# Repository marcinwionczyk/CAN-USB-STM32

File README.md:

# CAN-USB-STM32
this is a repository based on "TheRo0T/CAN-USB-STM32" repository. The difference is that I'm using STM32F303CCT6 microcontroller, SN65HVD230DR CAN interface and my own PCB design based on available parts.

PCBs was designed with Autodesk Eagle.

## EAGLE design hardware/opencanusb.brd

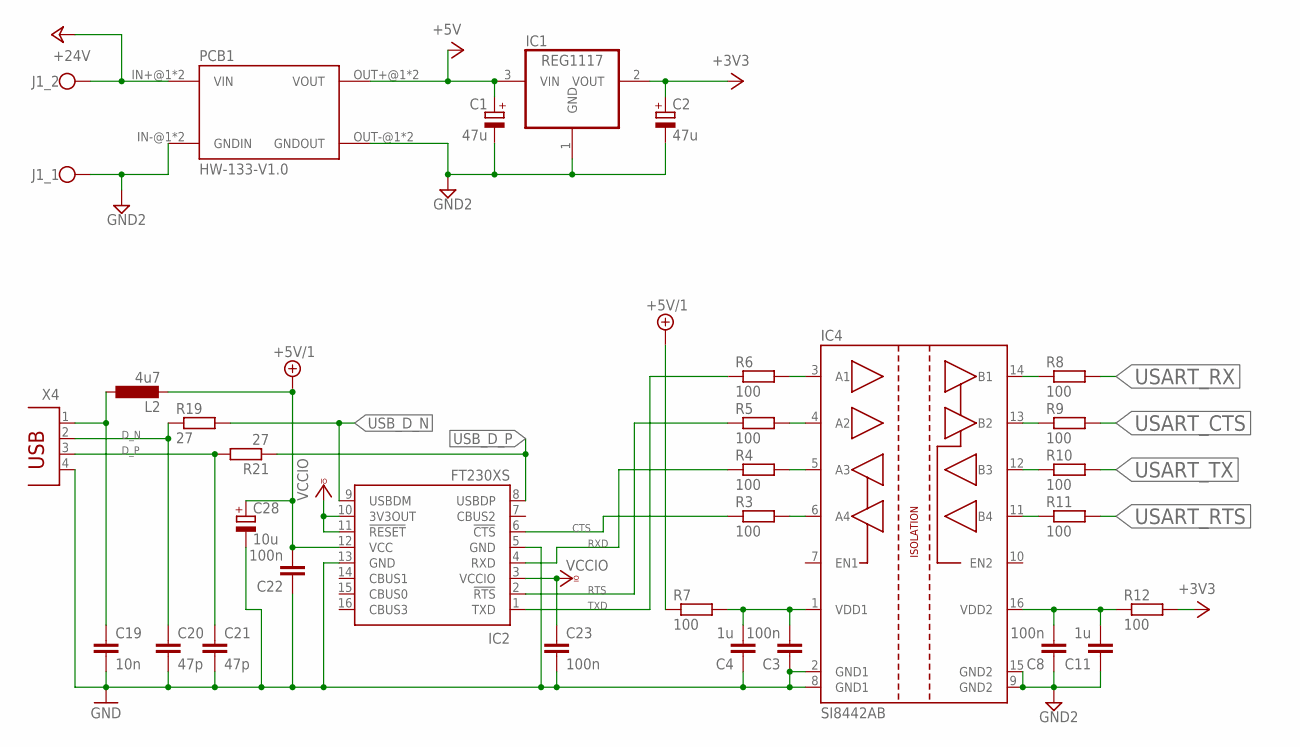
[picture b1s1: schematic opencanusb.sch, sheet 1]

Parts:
C1, C2: 47u; E1,8-4
C3, C8, C22, C23: 100n; C0805
C4, C11: 1u; C0805
C19: 10n; C0402
C20, C21: 47p; C0603
C28: 10u; SMC_A
IC1: REG1117; SOT223
IC2: FT230XS; SSOP16
IC4: SI8442AB; SOIC127P1030X265-16N
J1: DG300-7.5
L2: 4u7; L1812
PCB1: HW-133-V1.0; HW-133
R3, R4, R5, R6, R7, R8, R9, R10, R11, R12: 100; R0603
R19, R21: 27; R0805
X4: PN61729

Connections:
+3V3: C2.+, IC1.2 (VOUT), R12.2; also elsewhere on the board
+5V: C1.+, IC1.3 (VIN), PCB1.OUT+@1 (VOUT), PCB1.OUT+@2 (VOUT)
+5V/1: C22.2, C28.+, IC2.12 (VCC), L2.2, R7.1
+24V: J1.P$2, PCB1.IN+@1 (VIN), PCB1.IN+@2 (VIN)
CTS: IC2.6 (!CTS), R3.1
D_N: C20.1, R19.1, X4.2
D_P: C21.1, R21.2, X4.3
GND: C3.1, C4.1, C19.2, C20.2, C21.2, C22.1, C23.2, C28.-, IC2.5 (GND), IC2.13 (GND), IC4.2 (GND1), IC4.8 (GND1), X4.4
GND2: C1.-, C2.-, C8.1, C11.1, IC1.1 (GND), IC4.9 (GND2), IC4.15 (GND2), J1.P$1, PCB1.IN-@1 (GNDIN), PCB1.IN-@2 (GNDIN), PCB1.OUT-@1 (GNDOUT), PCB1.OUT-@2 (GNDOUT); also elsewhere on the board
unnamed: IC4.6 (A4), R3.2
unnamed: C3.2, C4.2, IC4.1 (VDD1), R7.2
unnamed: IC4.5 (A3), R4.2
unnamed: IC4.4 (A2), R5.2
unnamed: IC4.3 (A1), R6.2
unnamed: C8.2, C11.2, IC4.16 (VDD2), R12.1
unnamed: IC4.14 (B1), R8.1
unnamed: IC4.13 (B2), R9.1
unnamed: IC4.12 (B3), R10.1
unnamed: IC4.11 (B4), R11.1
unnamed: C19.1, L2.1, X4.1
RTS: IC2.2 (!RTS), R5.1
RXD: IC2.4 (RXD), R4.1
TXD: IC2.1 (TXD), R6.1
USART_CTS: R9.2; also elsewhere on the board
USART_RTS: R11.2; also elsewhere on the board
USART_RX: R8.2; also elsewhere on the board
USART_TX: R10.2; also elsewhere on the board
USB_D_N: IC2.9 (USBDM), R19.2
USB_D_P: IC2.8 (USBDP), R21.1
VCCIO: C23.1, IC2.3 (VCCIO), IC2.10 (3V3OUT), IC2.11 (!RESET)

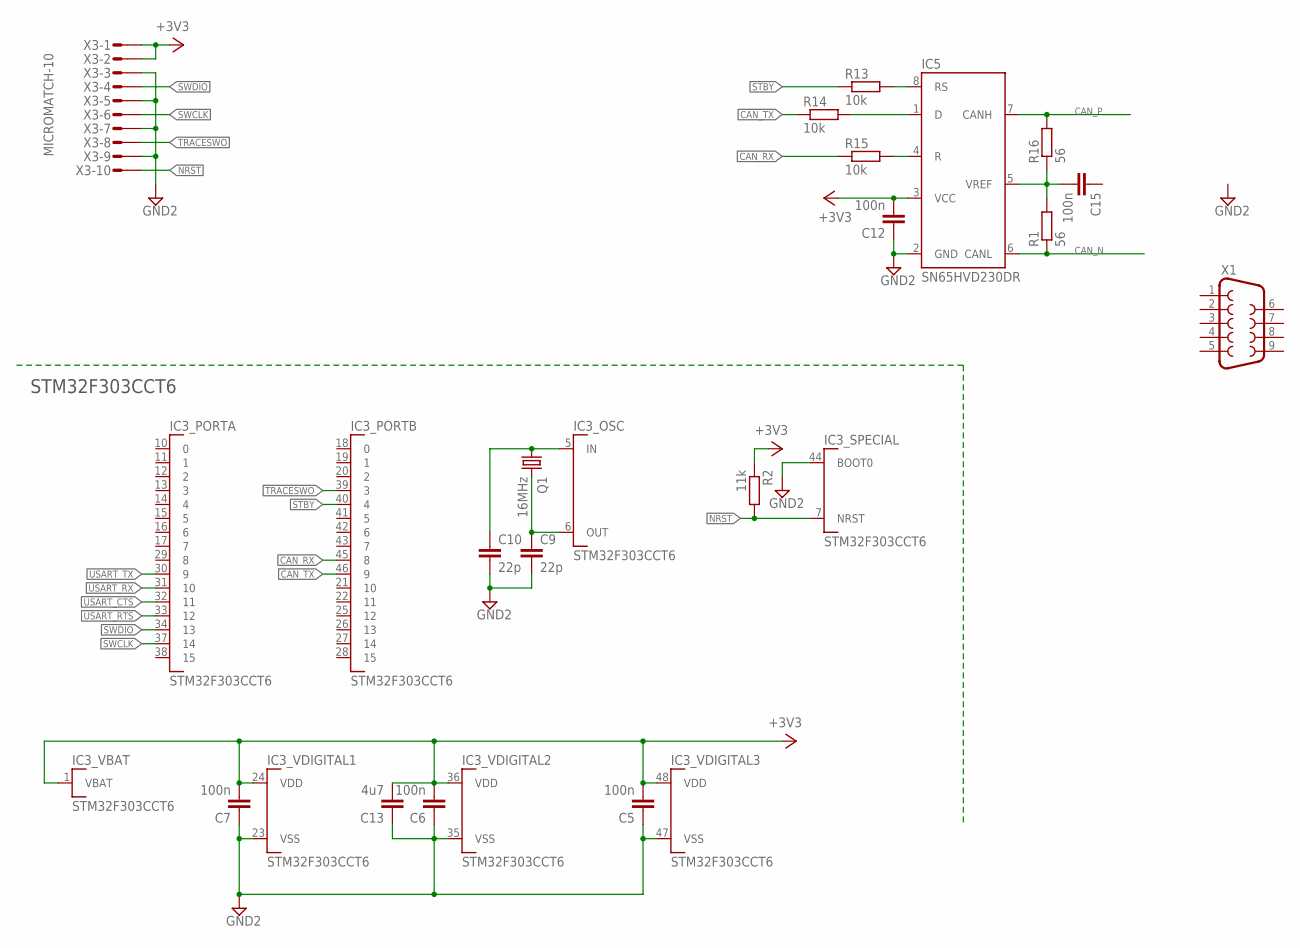
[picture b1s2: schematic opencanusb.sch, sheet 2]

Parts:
C5, C6, C7, C15: 100n; C0805
C9, C10: 22p; C0805
C12: 100n; C0402
C13: 4u7; C0805
IC3: STM32F303CCT6; QFP50P900X900X160-48N
IC5: SN65HVD230DR; SOIC127P599X175-8N
Q1: 16MHz; HC49UP
R1, R16: 56; R1206
R2: 11k; R1206
R13, R14, R15: 10k; R1206
X1: F09HP
X3: MICROMATCH-10

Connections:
+3V3: C5.2, C6.2, C7.2, C12.2, C13.2, IC3.1 (VBAT), IC3.24 (VDD), IC3.36 (VDD), IC3.48 (VDD), IC5.3 (VCC), R2.1, X3.1, X3.2; also elsewhere on the board
CAN_N: IC5.6 (CANL), R1.1
CAN_P: IC5.7 (CANH), R16.2
CAN_RX: IC3.45 (8), R15.1
CAN_TX: IC3.46 (9), R14.1
GND2: C5.1, C6.1, C7.1, C9.2, C10.2, C12.1, C13.1, IC3.23 (VSS), IC3.35 (VSS), IC3.44 (BOOT0), IC3.47 (VSS), IC5.2 (GND), X3.3, X3.5, X3.7, X3.9; also elsewhere on the board
unnamed: C15.2, IC5.5 (VREF), R1.2, R16.1
unnamed: IC5.8 (RS), R13.2
unnamed: IC5.1 (D), R14.2
unnamed: IC5.4 (R), R15.2
unnamed: C9.1, IC3.6 (OUT), Q1.2
unnamed: C10.1, IC3.5 (IN), Q1.1
NRST: IC3.7 (NRST), R2.2, X3.10
STBY: IC3.40 (4), R13.1
SWCLK: IC3.37 (14), X3.6
SWDIO: IC3.34 (13), X3.4
TRACESWO: IC3.39 (3), X3.8
USART_CTS: IC3.32 (11); also elsewhere on the board
USART_RTS: IC3.33 (12); also elsewhere on the board
USART_RX: IC3.31 (10); also elsewhere on the board
USART_TX: IC3.30 (9); also elsewhere on the board
VDDA: IC3.9 (VDDA)
VSSA: IC3.8 (VSSA)

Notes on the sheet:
STM32F303CCT6

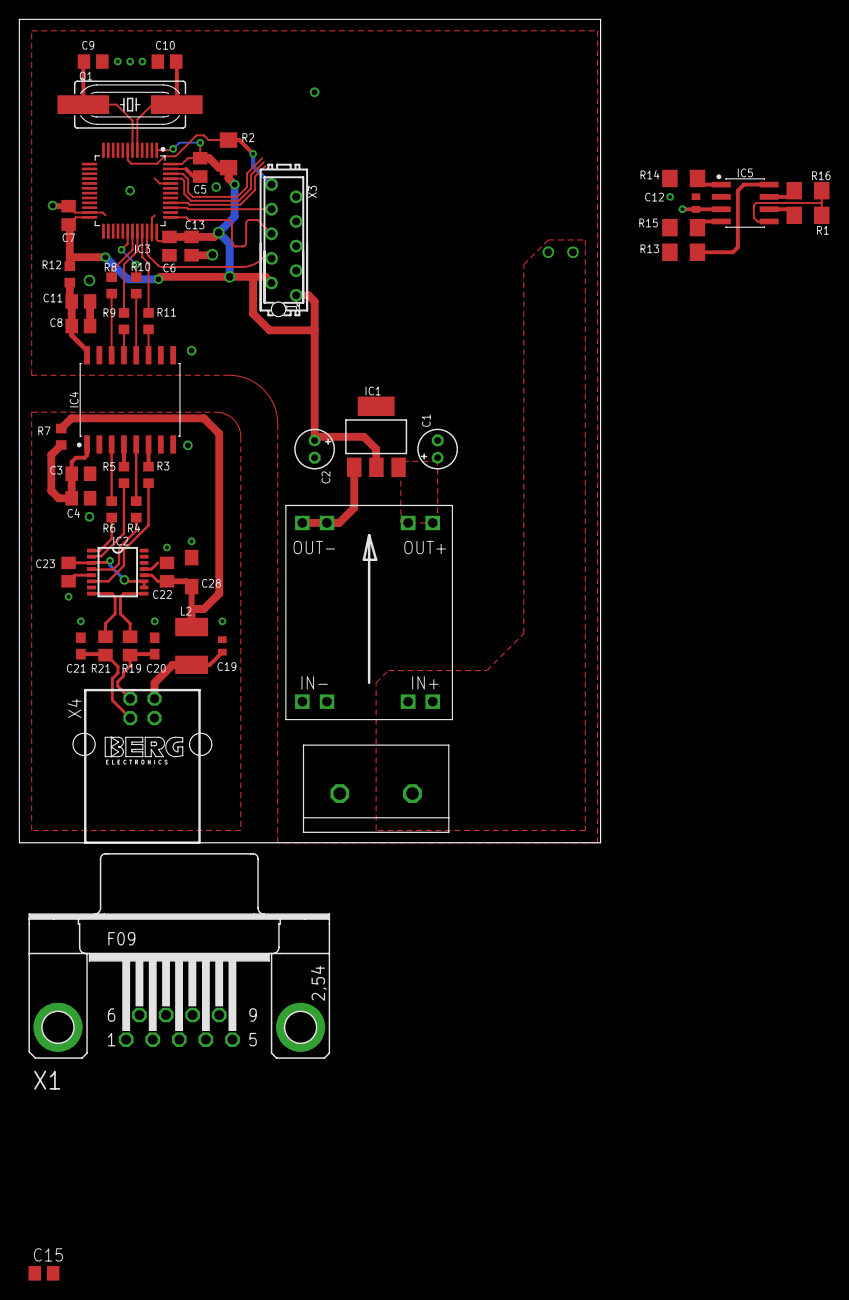
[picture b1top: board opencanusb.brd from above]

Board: 2 copper layers, 60.0 x 85.0 mm, 50 parts (0 on the bottom side), 45 nets.

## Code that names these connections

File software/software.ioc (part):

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Mcu.UserName=STM32F303CCTx
RCC.SYSCLKSourceVirtual=RCC_SYSCLKSOURCE_PLLCLK
PA11.Mode=CTS_RTS
RCC.HSEPLLFreq_Value=8000000
PB4.GPIOParameters=GPIO_Label
PA12.Signal=USART1_RTS
RCC.HSE_VALUE=16000000
PB3.Mode=Trace_Asynchronous_SW
PA14.Mode=Trace_Asynchronous_SW
Mcu.Package=LQFP48
PB9.Signal=CAN_TX
PA10.Signal=USART1_RX
PF1-OSC_OUT.Mode=HSE-External-Oscillator
PF1-OSC_OUT.Signal=RCC_OSC_OUT
PB4.Signal=GPIO_Output
PA10.Mode=Asynchronous
PA13.Signal=SYS_JTMS-SWDIO
PA9.Mode=Asynchronous
PB9.Mode=CAN_Activate
PA9.Signal=USART1_TX
PF0-OSC_IN.Mode=HSE-External-Oscillator
board=custom
PB4.GPIO_Label=STBY
PA13.Mode=Trace_Asynchronous_SW
Mcu.Name=STM32F303C(B-C)Tx
PB3.Signal=SYS_JTDO-TRACESWO
RCC.SYSCLKFreq_VALUE=72000000
PA12.Mode=CTS_RTS
PA11.Signal=USART1_CTS
PA14.Signal=SYS_JTCK-SWCLK
PB8.Mode=CAN_Activate
PB8.Signal=CAN_RX
PF0-OSC_IN.Signal=RCC_OSC_IN

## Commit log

2021-04-11 First commit. Not checked yet if it works.
2021-04-11 added images of pcb board
2021-04-17 added pdf file
2021-05-30 added stm32f3discovery.cfg
